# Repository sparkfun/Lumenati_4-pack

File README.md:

SparkFun Lumenati 4-pack
========================================

[*SparkFun Lumenati 4-pack (COM-14353)*](https://www.sparkfun.com/products/14353)

Designed to give your projects an edge in their lighting capacity, the SparkFun Lumenati 4-pack is a coin-sized board equipped with four APA102C LEDs surrounding the outer edge. The 4-pack board can be daisy-chained with other Lumenati boards, thanks to the multiple SMD pads on the back allowing for multiple design options and formations. 

Repository Contents
-------------------

* **/Hardware** - KiCad design files.
* **/Production** - Production panel files.

Documentation
--------------
* **[Example Code](https://github.com/sparkfun/SparkFun_Lumenati_Code)** - Python and Arduino example code for the Lumenati boards.
* **[FastLED Arduino Library](https://github.com/FastLED/FastLED)** - FastLED Arduino library when using the Lumenati with an Arduino.
* **[Hookup Guide](https://learn.sparkfun.com/tutorials/lumenati-hookup-guide)** - Basic hookup guide for the SparkFun Lumenati boards.

License Information
-------------------

This product is _**open source**_! 

Please review the LICENSE.md file for license information. 

If you have any questions or concerns on licensing, please contact techsupport@sparkfun.com.

Distributed as-is; no warranty is given.

- Your friends at SparkFun.

_<COLLABORATION CREDIT>_

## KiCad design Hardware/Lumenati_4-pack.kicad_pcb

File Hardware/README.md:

SparkFun <PRODUCT NAME> Design Files
=====================================

The .sch and .brd files hare are KiCad CAD schematic and PCB design files from SparkFun Electronics.
KiCad can be found at http://kicad-pcb.org/.

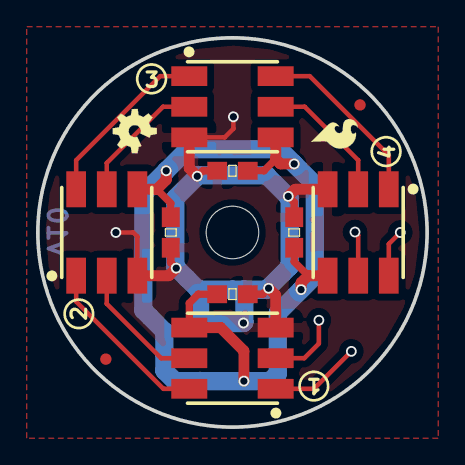
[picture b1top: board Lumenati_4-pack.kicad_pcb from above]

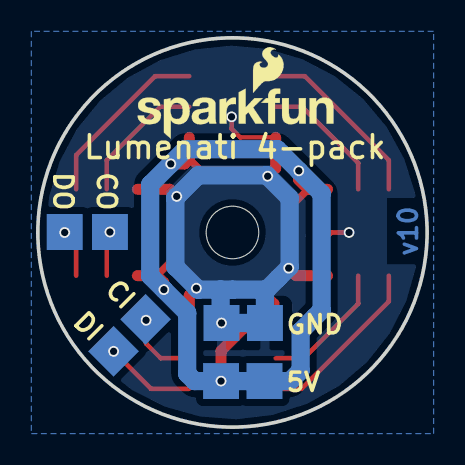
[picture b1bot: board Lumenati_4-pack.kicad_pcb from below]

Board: 2 copper layers, 21.6 x 21.6 mm, 17 parts (8 on the bottom side), 12 nets.

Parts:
C1, C2, C3, C4: C; 0603_revised
J1, J7: 5V; solder_pad_2
J2: CI; solder_pad_2
J3: DI; solder_pad_2
J4, J8: GND; solder_pad_2
J5: CO; solder_pad_2
J6: DO; solder_pad_2
Ref**: Val**; STAND-OFF_115_2
U1, U2, U3, U4: APA102C; APA102_3

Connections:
+5V: C1.1, C2.1, C3.1, C4.1, J1.1, J7.1, U1.4, U2.4, U3.4, U4.4
GND: C1.2, C2.2, C3.2, C4.2, J4.1, J8.1, U1.3, U2.3, U3.3, U4.3
unnamed: J2.1, U1.2
unnamed: J3.1, U1.1
unnamed: J5.1, U4.5
unnamed: J6.1, U4.6
unnamed: U1.5, U2.2
unnamed: U1.6, U2.1
unnamed: U2.5, U3.2
unnamed: U2.6, U3.1
unnamed: U3.5, U4.2
unnamed: U3.6, U4.1

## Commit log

2017-05-17 First commit of HiBeam_4-pack.
2017-05-18 Correcting with the proper directory structure.
2017-05-19 Fixes after double check.
2017-07-05 Silk fixes.
2017-08-11 Changed all the names to Lumenati, updated version to v10.
2017-08-18 Add fiducials to schematic.
2017-08-18 Set Edge_cuts outline to 8mil.
2017-08-18 panel
2017-08-21 Removing paste from fiducials.
2017-10-13 Update README.md
    Cleaning up to release repository,
2017-10-23 Update .gitignore to remove gers and other back up files.
2017-10-23 Forcibly removing gerbs and such
    Forcibly removing gerbs and such

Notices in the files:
Hardware/Lumenati_4-pack.kicad_pcb:
Released under the Creative Commons
Attribution Share-Alike 4.0 License
https://creativecommons.org/licenses/by-sa/4.0
